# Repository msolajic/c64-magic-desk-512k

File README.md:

# c64-magic-desk-512k
Hardware design of Magic Desk compatible C64 cartridge for up to 512k (expandable up to 1Mb)

This is the hardware part that accompanies the project of [Magic Desk Cartridge Generator](https://bitbucket.org/zzarko/magic-desk-cartridge-generator/)

This project is free to use and you can use any PCB manufacturer by downloading the Gerber files, but if you would like to support my work and help with further hardware development you can order these PCBs on PCBWay trough this link:

You will get cheap and professionally made PCBs, I will get credits that will help with this and [other projects](https://www.pcbway.com/project/member/?bmbno=1DE407A1-1650-47). Also, if you have to register to that site, [you can use this link](https://pcbway.com/g/YFnBAc) to get bonus initial credit.

Hardware Description
--------------------

Magic Desk cartridges, in their original form, could hold up to 128Kb of code, or up to 16 banks of 8Kb each. Bank selection is done by writing to $DE00. If bit 8 is set, then EXROM is disabled and RAM in the range of $8000 - $9FFF is usable.

This cartridge expands on the idea by having 128 banks of 8Kb available, thus the maximum size is 1 Mb.

Inputs of an 8-bit latch (74LS273) are connected to the data lines. Correct decoding for the I/O1 signal is done by combining PHI2 and I/O1 through the NOR gates of 74LS02. The only feature that is deviant from the original Magic Desk specification, is that when you disable the cartridge by writing a value of $80 or larger to $DE00, the banking mechanism gets locked and no more write attempts to $DE00 will change the register's state until a hardware reset is performed. This had to be done because some programs would unintentionally write to $DE00 (or any other location in the I/O1 range) and sometimes, if $01 is wrongly set by the program, it could result in a crash. Since the use of this particular cartridge is primarily to enable making onefile program compilations, we have decided to do it this way. If you want (or need) full compatibility with the original Magic Desk cartridge hardware, we have left a jumper to disable this behaviour. Cut the track exposed on the LOCK / NO LOCK jumper on the bottom side of the cartridge PCB, and connect it the other way around. This way the locking mechanism is disabled, but still you can remove the cartridge from the memory map by setting the bit 7 of the latch high.

The PCB was designed to accomodate various types of EPROMs and their FLASH variants. The smallest EPROM you can use is 27C512 (64Kb), and the largest is 27C040 (512Kb). There is an option to expand the board to a full 1Mb, which will be explained below.

Jumper configuration
--------------------

In order to support all possible types of EPROMs and FLASH EPROMs, a bank of solder jumpers had to be placed on the bottom side of the PCB. They look like this:

```
JA17 [X X X]       
JA18 [X X X]      
 JF  [X X X]      
JA16 [X X X]
```

These jumpers HAVE to be configured before plugging the cartridge to your C64! Different types of EPROMs and their FLASH variants have some pins swapped, and if you are using a chip smaller than the maximum size, the unused adress lines have to be pulled high on the EPROM side to ensure proper functioning. Also, 27C512 is "shorter" by 4 pins, so its power supply pin must be connected to +5V instead of being allocated as A17 on the larger ones. The rightmost pins of all 4 jumpers are +5V, and the leftmost pins are the address lines. The middle pin of the jumpers are connected according to the table:

| Jumper | Pin | Description                                 |
|--------|-----|---------------------------------------------|
| JA16   | 2   | routes either A16 or VCC to pin 2 of EPROM  |
| JA17   | 30  | routes either A17 or VCC to pin 30 of EPROM |
| JA18   | 1   | routes either A18 or VCC to pin 1 of EPROM  |
| JF     | 31  | routes either A18 or VCC to pin 31 of EPROM |

Here is the table for configuring the jumpers on most common variants of EPROMS and their FLASH counterparts.

```
   27C512          27C010          29F010          27C020          29F020          27C040          29F040
   ------          ------          ------          ------          ------          ------          ------

JA17 [X X=X]    JA17 [X X X]    JA17 [X X X]    JA17 [X=X X]    JA17 [X=X X]    JA17 [X=X X]    JA17 [X=X X]
JA18 [X X X]    JA18 [X X=X]    JA18 [X X X]    JA18 [X X=X]    JA18 [X X=X]    JA18 [X X=X]    JA18 [X=X X]
 JF  [X X X]     JF  [X X=X]     JF  [X X=X]     JF  [X X=X]     JF  [X X=X]     JF  [X=X X]     JF  [X X=X]
JA16 [X X X]    JA16 [X=X X]    JA16 [X=X X]    JA16 [X=X X]    JA16 [X=X X]    JA16 [X=X X]    JA16 [X=X X]
```

Precautions have been taken to ensure the correctness of the table above. Please, check the datasheet of your particular (FLASH) EPROM and configure the jumpers accordingly.

Beyond 512Kb
------------

Full 1Mb is achievable by piggybacking one EPROM to another (essentially making a tower) and should be done only with 27C040 / 29F040 types of memory. Pin 22 of the EPROMs is the only one that should not be connected together. After piggybacking the EPROMs, run a wire from the exposed pad CE2 to pin 22 of the top EPROM. PCB design for a dual EPROM variant will be available soon.

RESET button
------------

The pads for the RESET button will accomodate either a vertical or horizontal miniature tact switch, and the two pads are there to help you to run a wire for a switch if you are putting the PCB in a cartridge case.

Enclosure compatibility
-----------------------

The PCB is designed so it can be used in various types of cartridge cases. It has been designed to fit the original Commodore cases and cases from the Polish companies KRADEX / MASZCZYK which are available at some retailers in Europe. It also fits in a 3D-printed case from the model available at Thingiverse. Unfortunately, we don't have all of the cartridge cases available in the market, so the design is NOT tested to fit with: Individual Computers', TFW8B and Shareware Plus' (and all other currently available) cases. If anyone wants to donate these types of cartridge cases, adjustments to the PCB could be made and a "one board fits all" PCB could be produced.
Please note - the cartridge cases from KRADEX / MASZCZYK are "low profile", and you cannot use a socket for the EPROM with these types of cases!

Copyright
---------

Cartridge schematics and PCB design (c) 2013-2019 Marko Šolajić

Released under GNU General Public License v3.0, see LICENSE file.

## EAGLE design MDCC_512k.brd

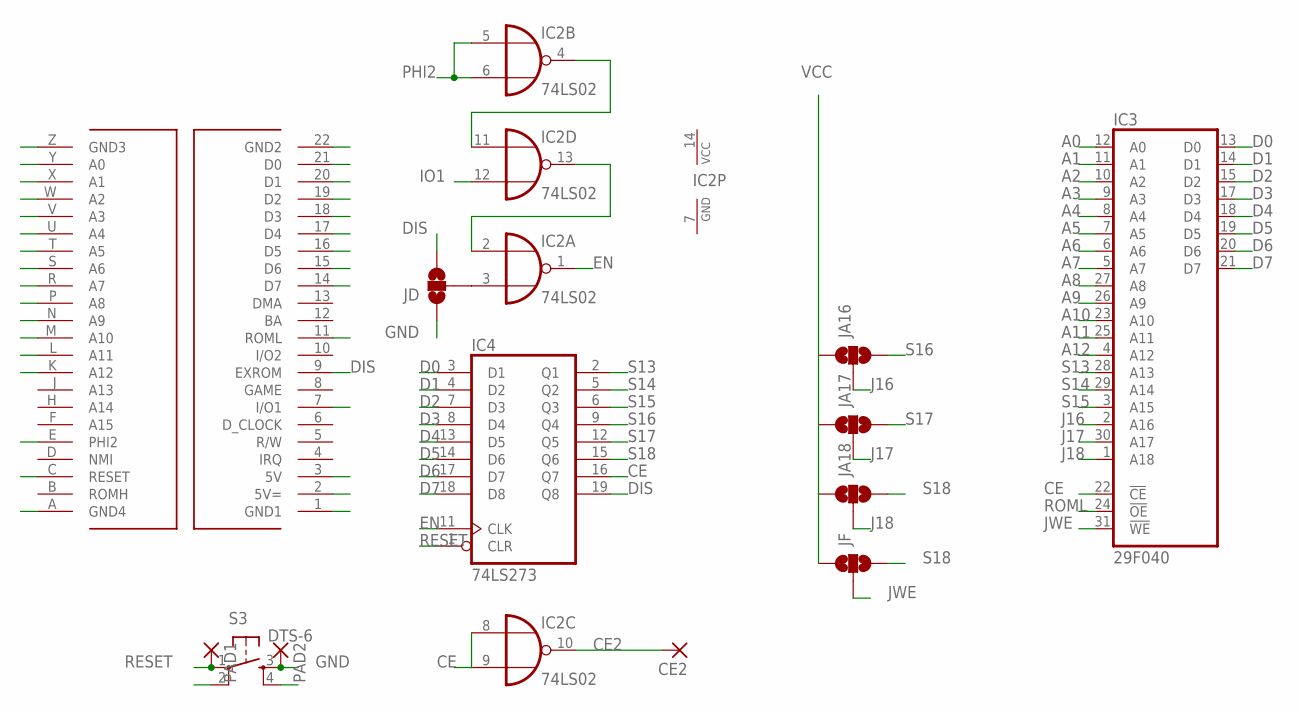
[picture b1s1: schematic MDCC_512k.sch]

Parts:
CE2: 1,6/0,9
IC2: 74LS02; DIL14
IC3: 29F040; DIL32-6
IC4: 74LS273; DIL20
JA16, JA17, JA18: SOLDERJUMPER_2WAYS; SJ_3
JD: SOLDERJUMPER_2WAYS; SJ_3
JF: SOLDERJUMPER_2WAYS; SJ_3
PAD1, PAD2: SMD5; SMD2,54-5,08
S3: DTS-6
U$1: C64_EXPANSION__CARTRIDGE

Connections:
A0: IC3.12 (A0), U$1.Y (A0)
A1: IC3.11 (A1), U$1.X (A1)
A2: IC3.10 (A2), U$1.W (A2)
A3: IC3.9 (A3), U$1.V (A3)
A4: IC3.8 (A4), U$1.U (A4)
A5: IC3.7 (A5), U$1.T (A5)
A6: IC3.6 (A6), U$1.S (A6)
A7: IC3.5 (A7), U$1.R (A7)
A8: IC3.27 (A8), U$1.P (A8)
A9: IC3.26 (A9), U$1.N (A9)
A10: IC3.23 (A10), U$1.M (A10)
A11: IC3.25 (A11), U$1.L (A11)
A12: IC3.4 (A12), U$1.K (A12)
CE: IC2.8 (I0), IC2.9 (I1), IC3.22 (!CE), IC4.16 (Q7)
CE2: CE2.1, IC2.10 (O)
D0: IC3.13 (D0), IC4.3 (D1), U$1.21 (D0)
D1: IC3.14 (D1), IC4.4 (D2), U$1.20 (D1)
D2: IC3.15 (D2), IC4.7 (D3), U$1.19 (D2)
D3: IC3.17 (D3), IC4.8 (D4), U$1.18 (D3)
D4: IC3.18 (D4), IC4.13 (D5), U$1.17 (D4)
D5: IC3.19 (D5), IC4.14 (D6), U$1.16 (D5)
D6: IC3.20 (D6), IC4.17 (D7), U$1.15 (D6)
D7: IC3.21 (D7), IC4.18 (D8), U$1.14 (D7)
DIS: IC4.19 (Q8), JD.3, U$1.9 (EXROM)
EN: IC2.1 (O), IC4.11 (CLK)
GND: IC2.7 (GND), IC3.16 (GND), IC4.10 (GND), JD.1, PAD2.1, S3.3, S3.4, U$1.1 (GND1), U$1.22 (GND2), U$1.A (GND4), U$1.Z (GND3)
IO1: IC2.12 (I1), U$1.7 (I/O1)
J16: IC3.2 (A16), JA16.2
J17: IC3.30 (A17), JA17.2
J18: IC3.1 (A18), JA18.2
JWE: IC3.31 (!WE), JF.2
unnamed: IC2.3 (I1), JD.2
unnamed: IC2.4 (O), IC2.11 (I0)
unnamed: IC2.2 (I0), IC2.13 (O)
PHI2: IC2.5 (I0), IC2.6 (I1), U$1.E (PHI2)
RESET: IC4.1 (CLR), PAD1.1, S3.1, S3.2, U$1.C (RESET)
ROML: IC3.24 (!OE), U$1.11 (ROML)
S13: IC3.28 (A13), IC4.2 (Q1)
S14: IC3.29 (A14), IC4.5 (Q2)
S15: IC3.3 (A15), IC4.6 (Q3)
S16: IC4.9 (Q4), JA16.3
S17: IC4.12 (Q5), JA17.3
S18: IC4.15 (Q6), JA18.3, JF.3
VCC: IC2.14 (VCC), IC3.32 (VCC), IC4.20 (VCC), JA16.1, JA17.1, JA18.1, JF.1, U$1.2 (5V=), U$1.3 (5V)

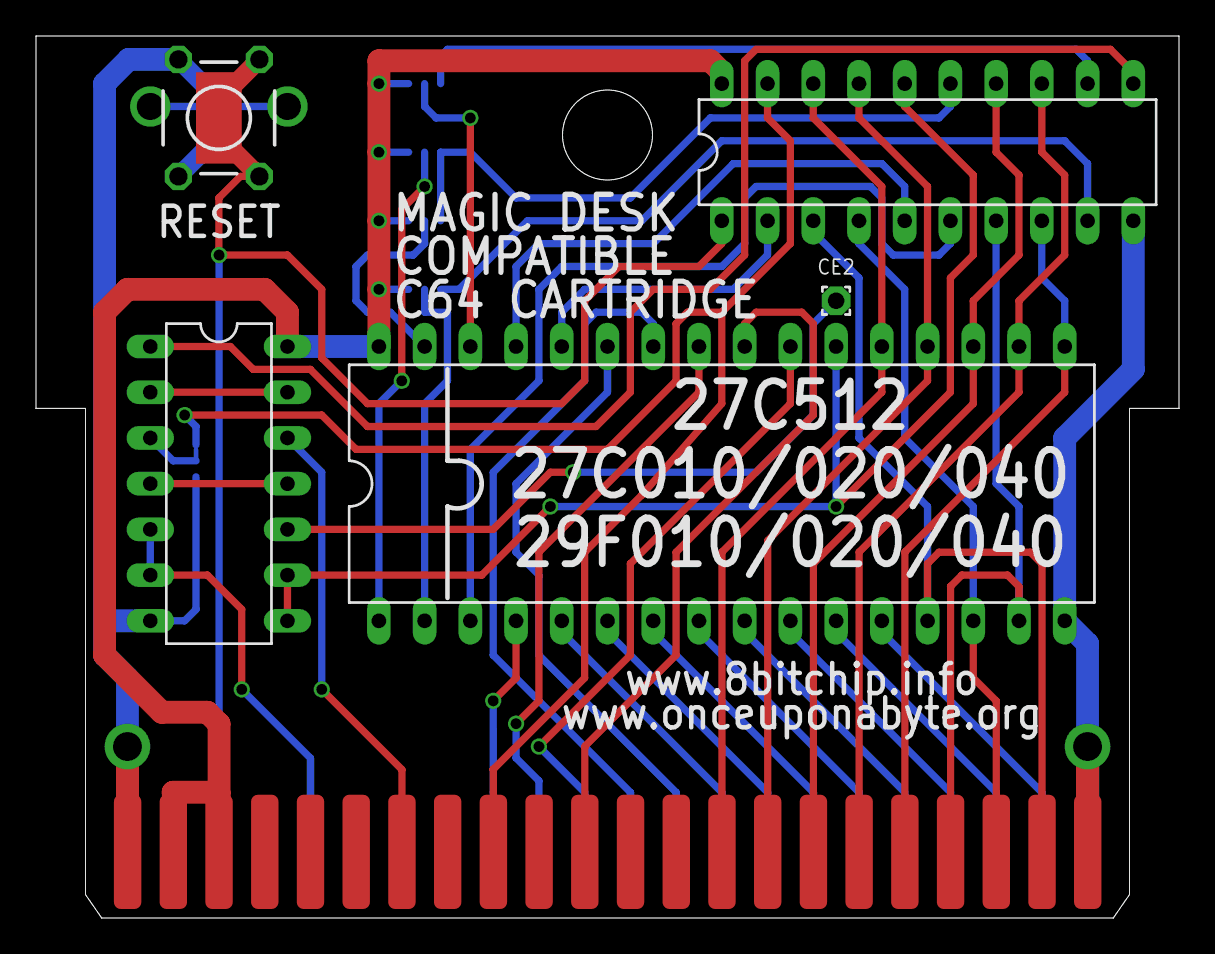
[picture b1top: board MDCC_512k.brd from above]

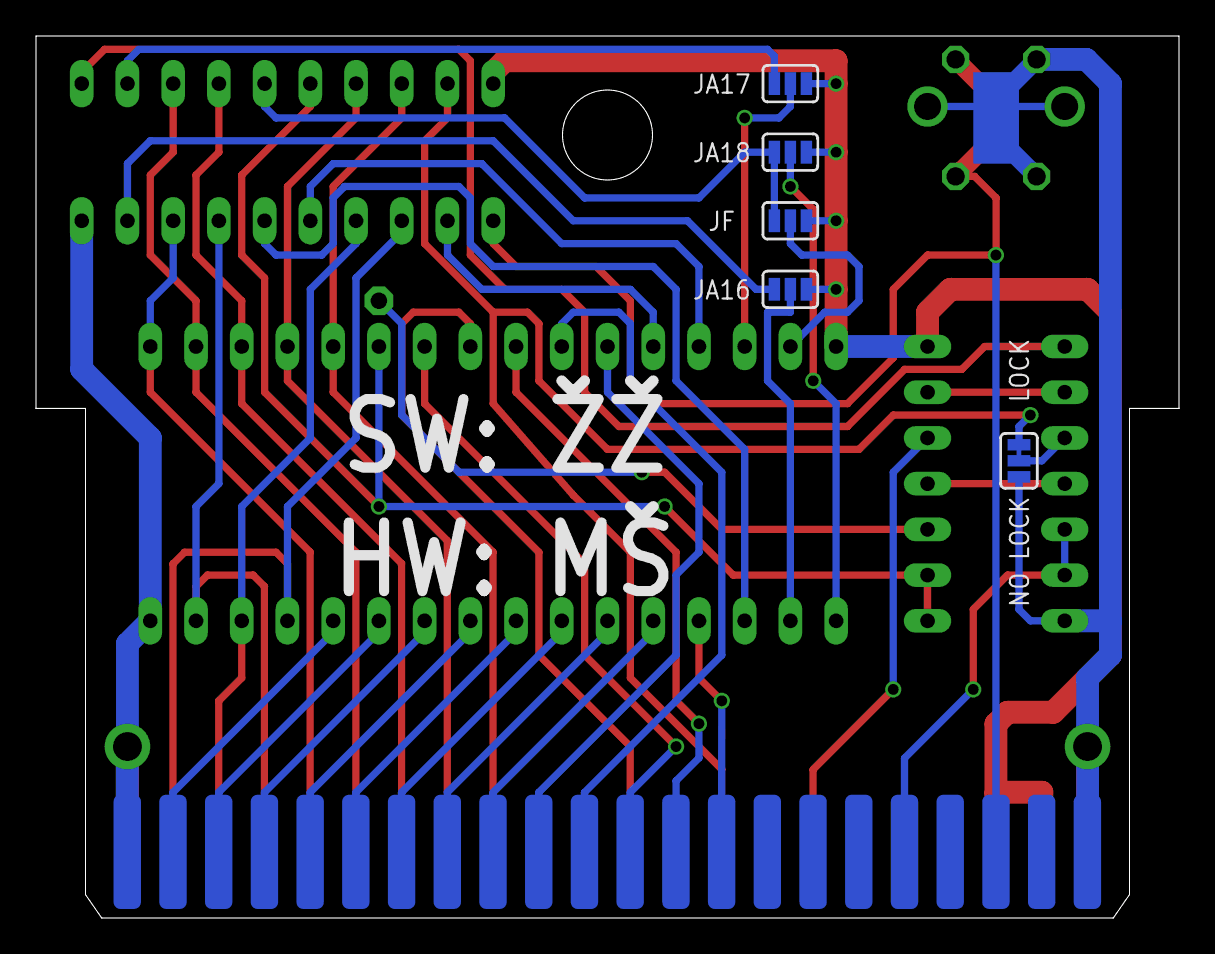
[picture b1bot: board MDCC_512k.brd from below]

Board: 2 copper layers, 63.5 x 49.0 mm, 13 parts (6 on the bottom side), 44 nets.

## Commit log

2022-01-13 pin 20 -> pin 22 in "Beyond 512Kb" section minor typos

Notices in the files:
parts and their libraries:
SparkFun-Passives: Licensing: CC v3.0 Share-Alike You are welcome to use this library for commercial purposes.
